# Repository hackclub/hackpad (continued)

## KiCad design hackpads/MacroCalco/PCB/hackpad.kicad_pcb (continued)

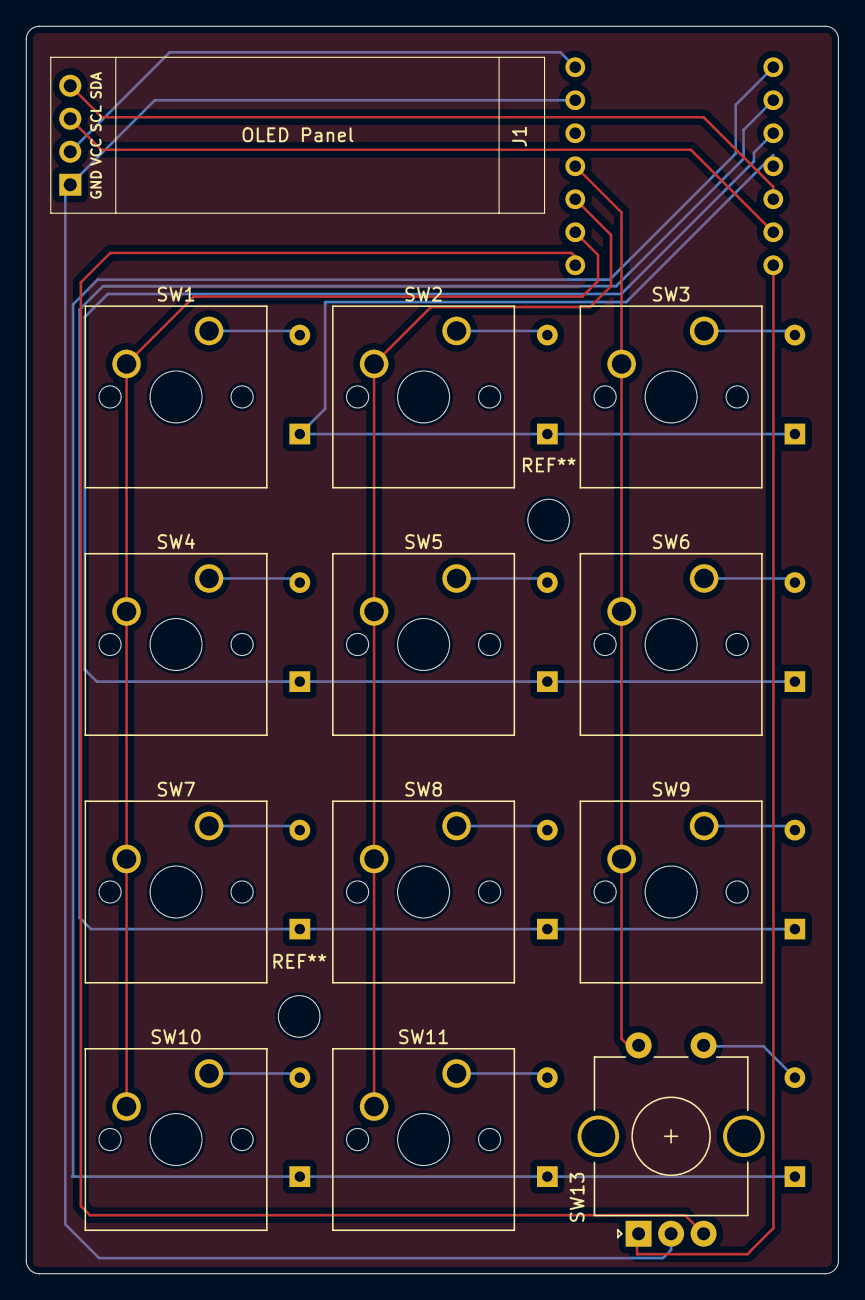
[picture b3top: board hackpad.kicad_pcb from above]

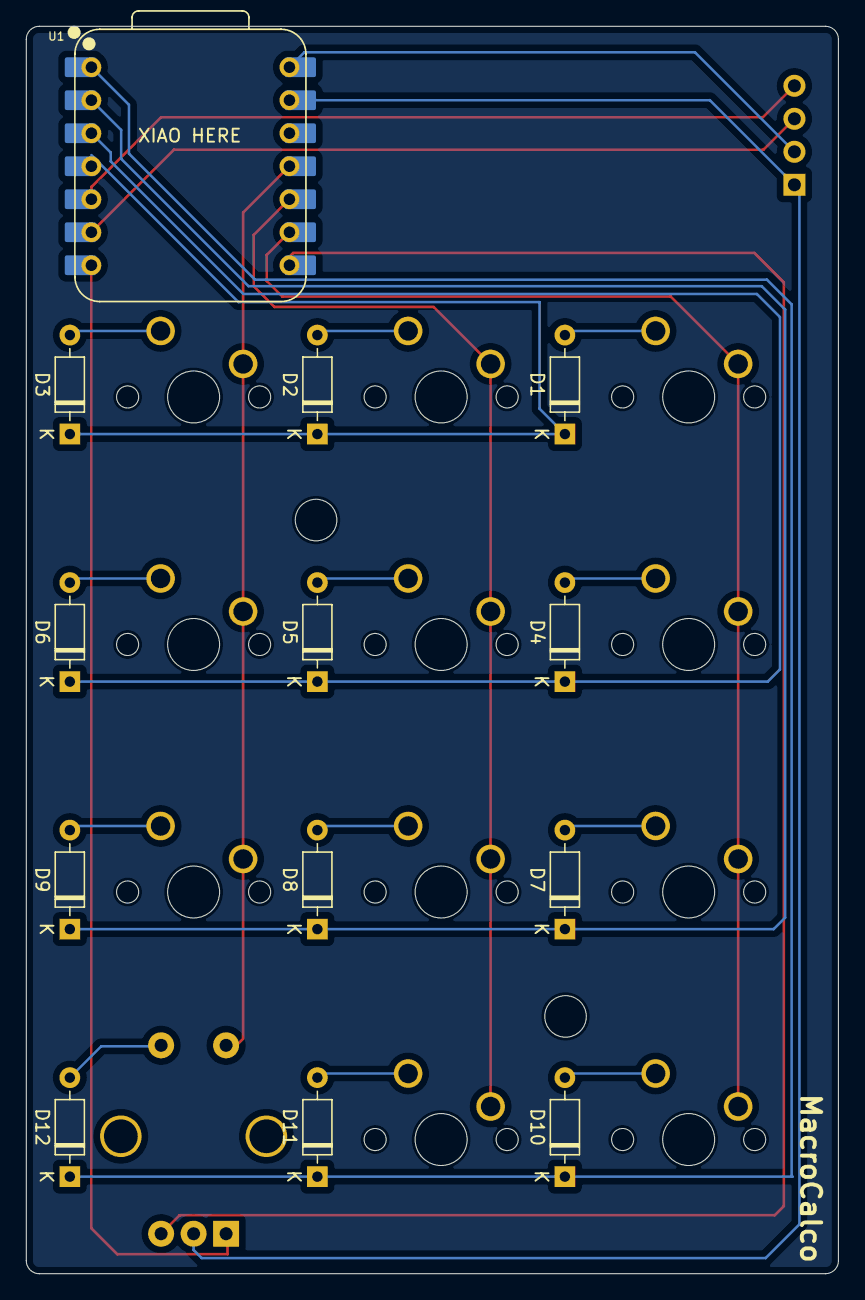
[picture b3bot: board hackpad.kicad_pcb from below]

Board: 2 copper layers, 62.5 x 96.0 mm, 26 parts (13 on the bottom side), 25 nets.

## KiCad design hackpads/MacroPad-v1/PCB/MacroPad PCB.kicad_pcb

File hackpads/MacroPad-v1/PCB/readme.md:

Macropad Project

Overview

This project is a custom macropad featuring 4 buttons and 1 rotary encoder, powered by the XIAO RP2040 microcontroller. It is designed to work with QMK firmware for customizable key mappings and enhanced functionality.

Features

Microcontroller: XIAO RP2040

Inputs: 4 mechanical keys, 1 rotary encoder

Firmware: QMK compatible

Connectivity: USB-C

Customizable: Fully programmable key functions via QMK firmware

Hardware Requirements

XIAO RP2040 microcontroller

4 mechanical key switches

1 rotary encoder with push button

PCB designed in KiCad (MacroPad.kicad_pcb)

USB-C cable for power and programming

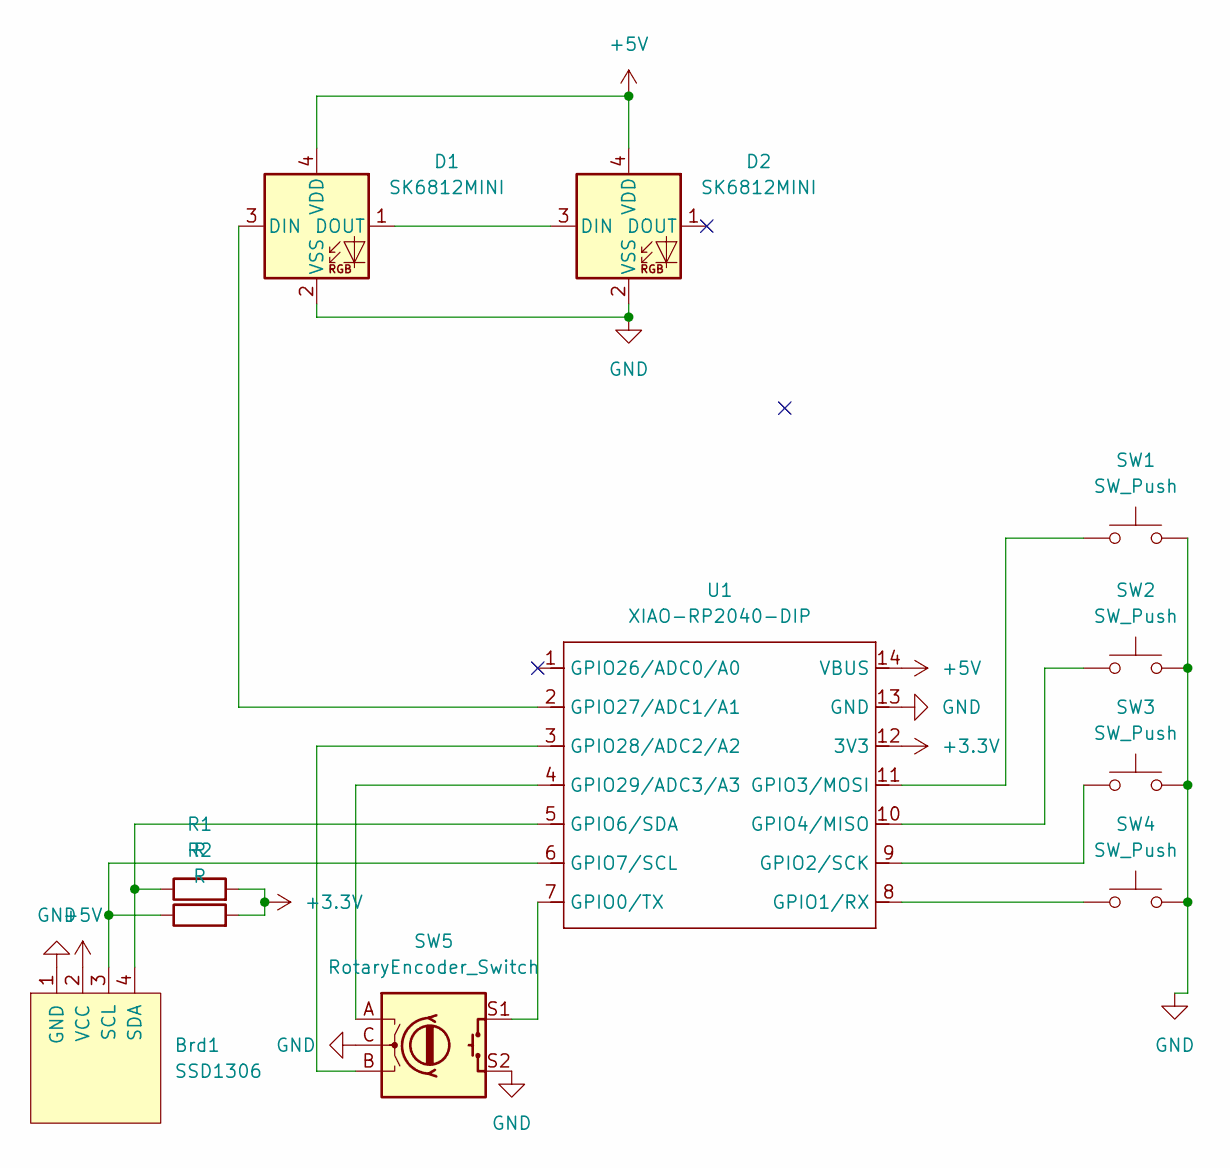
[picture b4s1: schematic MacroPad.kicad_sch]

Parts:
Brd1: SSD1306; 128x64OLED
D1, D2: SK6812MINI; LED_SK6812MINI_PLCC4_3.5x3.5mm_P1.75mm
R1, R2: R; R_Axial_DIN0204_L3.6mm_D1.6mm_P7.62mm_Horizontal
SW1, SW2, SW3, SW4: SW_Push; SW_Cherry_MX_1.00u_PCB
SW5: RotaryEncoder_Switch; RotaryEncoder_Alps_EC11E-Switch_Vertical_H20mm_CircularMoun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
U1: XIAO-RP2040-DIP

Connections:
+3.3V: R1.2, R2.2, U1.12 (3V3)
+5V: Brd1.2 (VCC), D1.4 (VDD), D2.4 (VDD), U1.14 (VBUS)
GND: Brd1.1 (GND), D1.2 (VSS), D2.2 (VSS), SW1.1, SW2.1, SW3.1, SW4.1, SW5.C, SW5.S2, U1.13 (GND)
unnamed: Brd1.3 (SCL), R2.1, U1.6 (GPIO7/SCL)
unnamed: Brd1.4 (SDA), R1.1, U1.5 (GPIO6/SDA)
unnamed: D1.3 (DIN), U1.2 (GPIO27/ADC1/A1)
unnamed: D1.1 (DOUT), D2.3 (DIN)
unnamed: SW5.S1, U1.7 (GPIO0/TX)
unnamed: SW4.2, U1.8 (GPIO1/RX)
unnamed: SW3.2, U1.9 (GPIO2/SCK)
unnamed: SW1.2, U1.11 (GPIO3/MOSI)
unnamed: SW2.2, U1.10 (GPIO4/MISO)
unnamed: SW5.B, U1.3 (GPIO28/ADC2/A2)
unnamed: SW5.A, U1.4 (GPIO29/ADC3/A3)

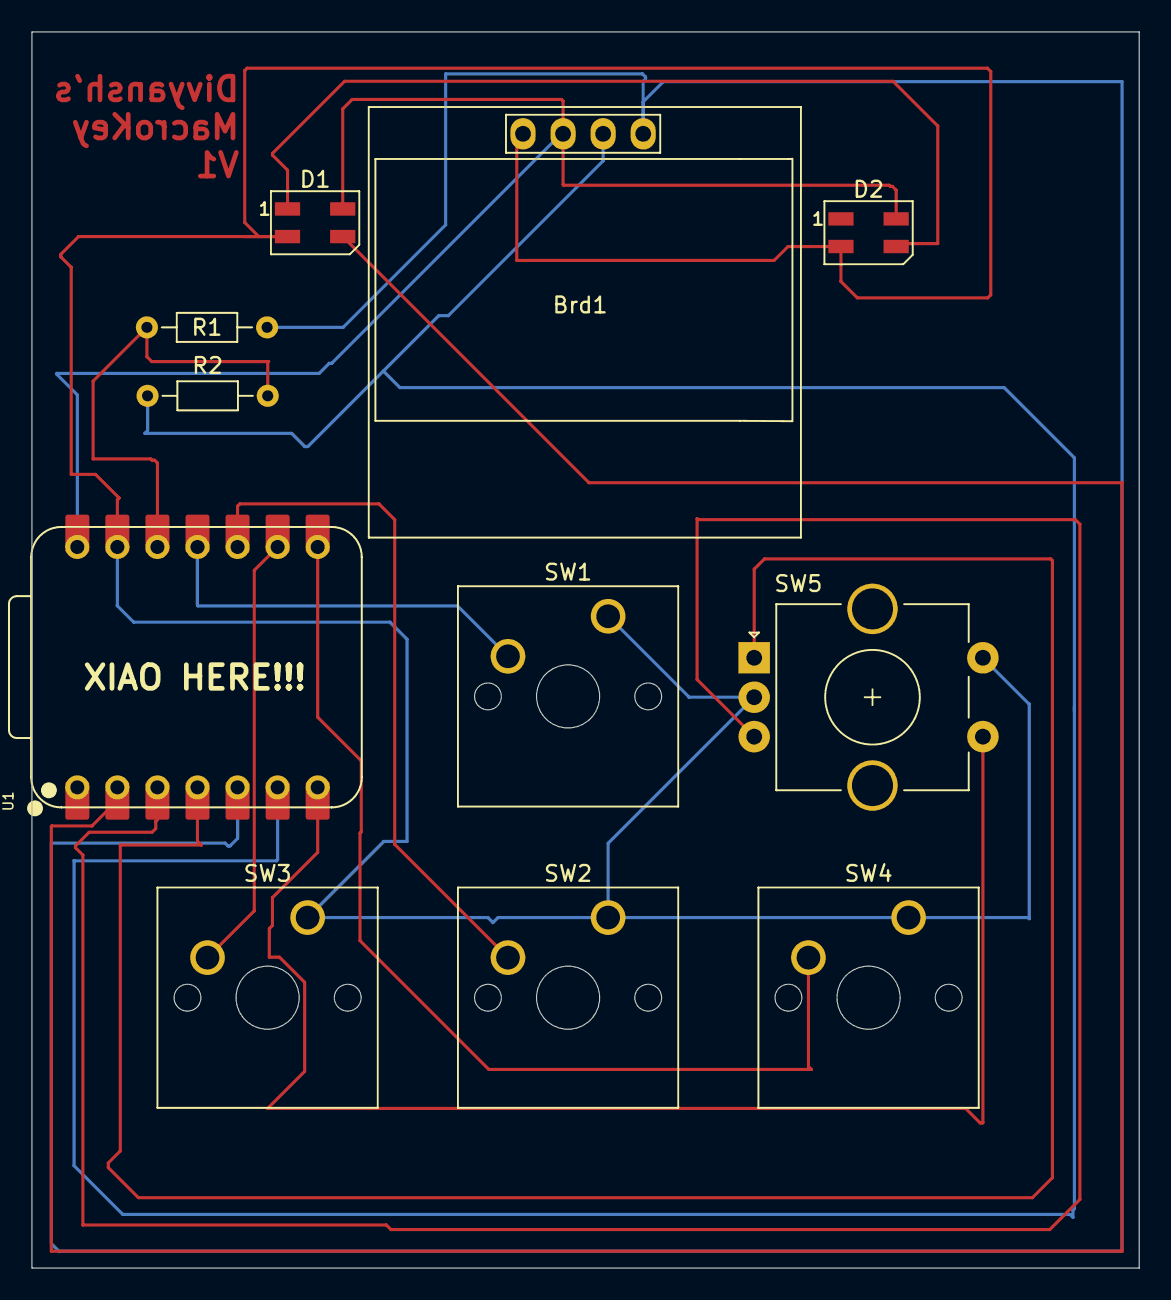
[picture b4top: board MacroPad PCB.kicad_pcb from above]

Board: 2 copper layers, 70.2 x 78.4 mm, 11 parts (0 on the bottom side), 14 nets.

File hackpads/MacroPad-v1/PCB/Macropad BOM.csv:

Reference	Value	Datasheet	Footprint	Qty	DNP
Brd1	SSD1306		SSD1306:128x64OLED	1	
D1,D2	SK6812MINI	https://cdn-shop.adafruit.com/product-files/2686/SK6812MINI_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	LED_SMD:LED_SK6812MINI_PLCC4_3.5x3.5mm_P1.75mm	2	
R1,R2	4.7kΩ	~	Resistor_THT:R_Axial_DIN0204_L3.6mm_D1.6mm_P7.62mm_Horizontal	2	
SW1,SW2,SW3,SW4	SW_Push	~	Button_Switch_Keyboard:SW_Cherry_MX_1.00u_PCB	4	
SW5	RotaryEncoder_Switch	~	Rotary_Encoder:RotaryEncoder_Alps_EC11E-Switch_Vertical_H20mm_CircularMountingHoles	1	
U1	XIAO-RP2040-DIP		OPL:XIAO-RP2040-DIP	1

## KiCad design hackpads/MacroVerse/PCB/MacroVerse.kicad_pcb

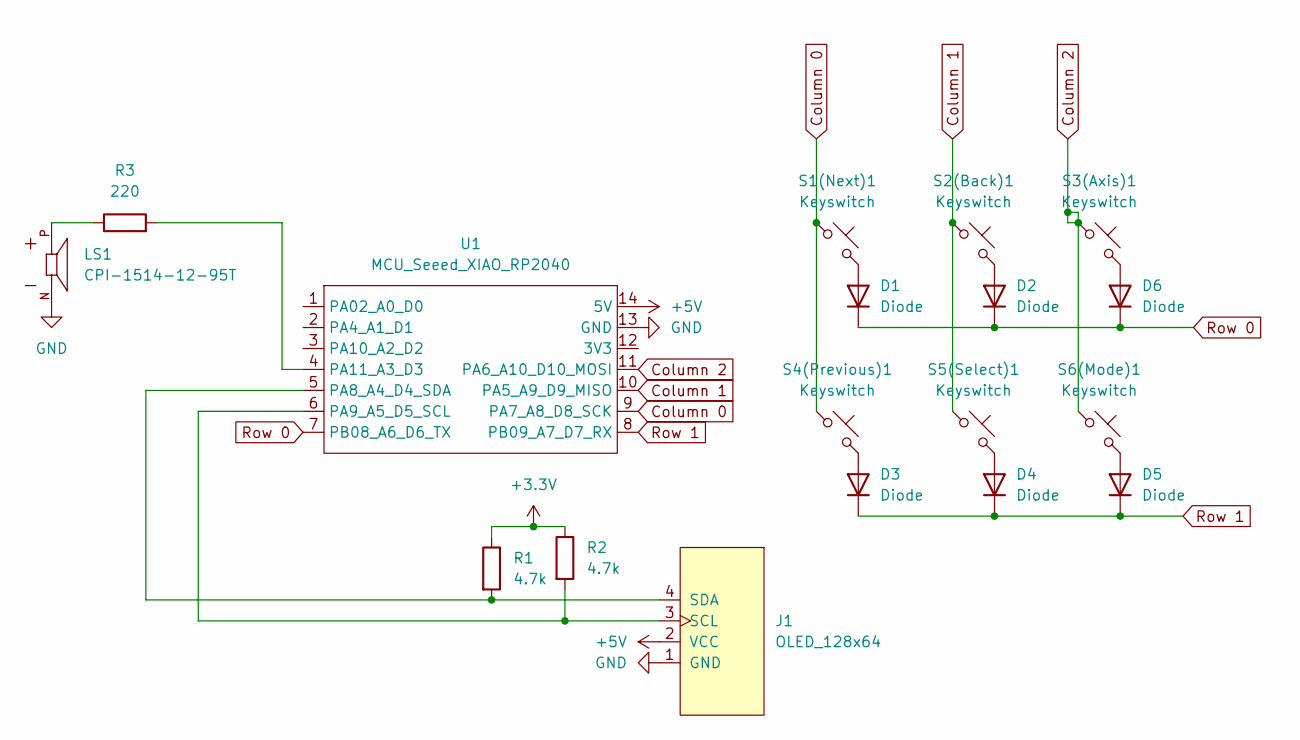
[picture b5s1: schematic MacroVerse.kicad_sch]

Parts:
D1, D2, D3, D4, D5, D6: Diode; Diode_DO-35
J1: OLED_128x64
LS1: CPI-1514-12-95T; XDCR_CPI-1514-12-95T; PARTREV 1.0
R1, R2: 4.7k; R_Axial_DIN0207_L6.3mm_D2.5mm_P7.62mm_Horizontal
R3: 220; R_Axial_DIN0207_L6.3mm_D2.5mm_P7.62mm_Horizontal
S1(Next)1, S2(Back)1, S3(Axis)1, S4(Previous)1, S5(Select)1, S6(Mode)1: Keyswitch; MX_PCB_1.00u
U1: MCU_Seeed_XIAO_RP2040; Seeed_XIAO_RP2040

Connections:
+3.3V: R1.1, R2.1
+5V: J1.2 (VCC), U1.14 (5V)
Column 0: S1(Next)1.1, S4(Previous)1.1, U1.9 (PA7_A8_D8_SCK)
Column 1: S2(Back)1.1, S5(Select)1.1, U1.10 (PA5_A9_D9_MISO)
Column 2: S3(Axis)1.1, S6(Mode)1.1, U1.11 (PA6_A10_D10_MOSI)
GND: J1.1 (GND), LS1.N, U1.13 (GND)
unnamed: D1.2 (A), S1(Next)1.2
unnamed: D2.2 (A), S2(Back)1.2
unnamed: D3.2 (A), S4(Previous)1.2
unnamed: D4.2 (A), S5(Select)1.2
unnamed: D5.2 (A), S6(Mode)1.2
unnamed: D6.2 (A), S3(Axis)1.2
unnamed: J1.3 (SCL), R2.2, U1.6 (PA9_A5_D5_SCL)
unnamed: J1.4 (SDA), R1.2, U1.5 (PA8_A4_D4_SDA)
unnamed: LS1.P, R3.1
unnamed: R3.2, U1.4 (PA11_A3_D3)
Row 0: D1.1 (K), D2.1 (K), D6.1 (K), U1.7 (PB08_A6_D6_TX)
Row 1: D3.1 (K), D4.1 (K), D5.1 (K), U1.8 (PB09_A7_D7_RX)

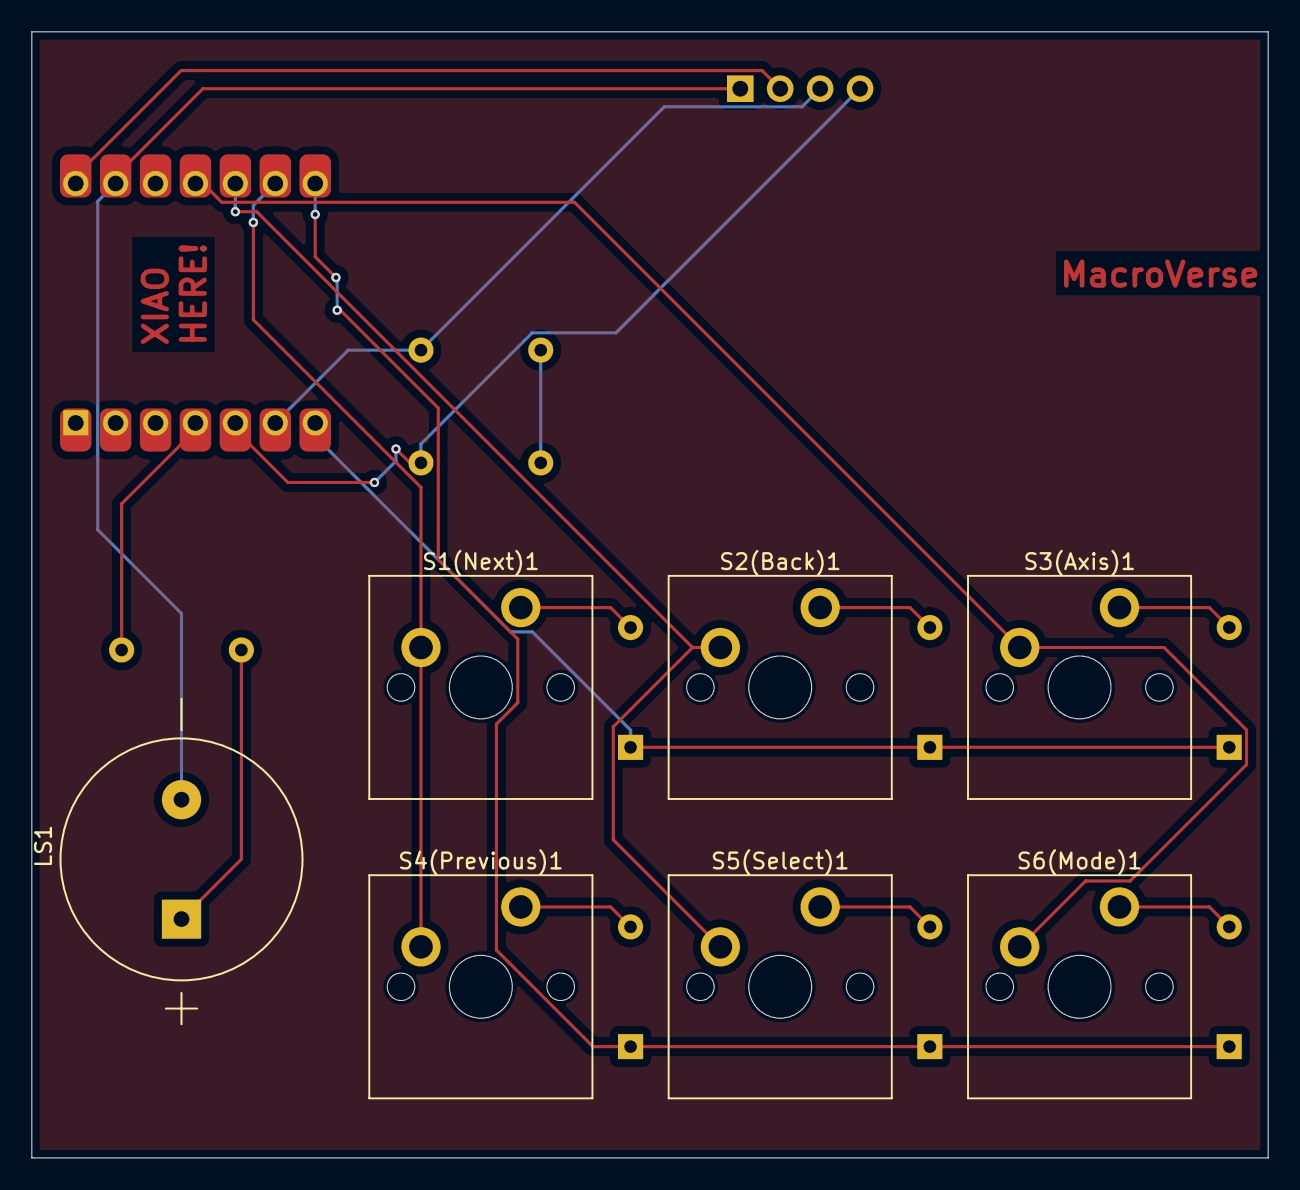
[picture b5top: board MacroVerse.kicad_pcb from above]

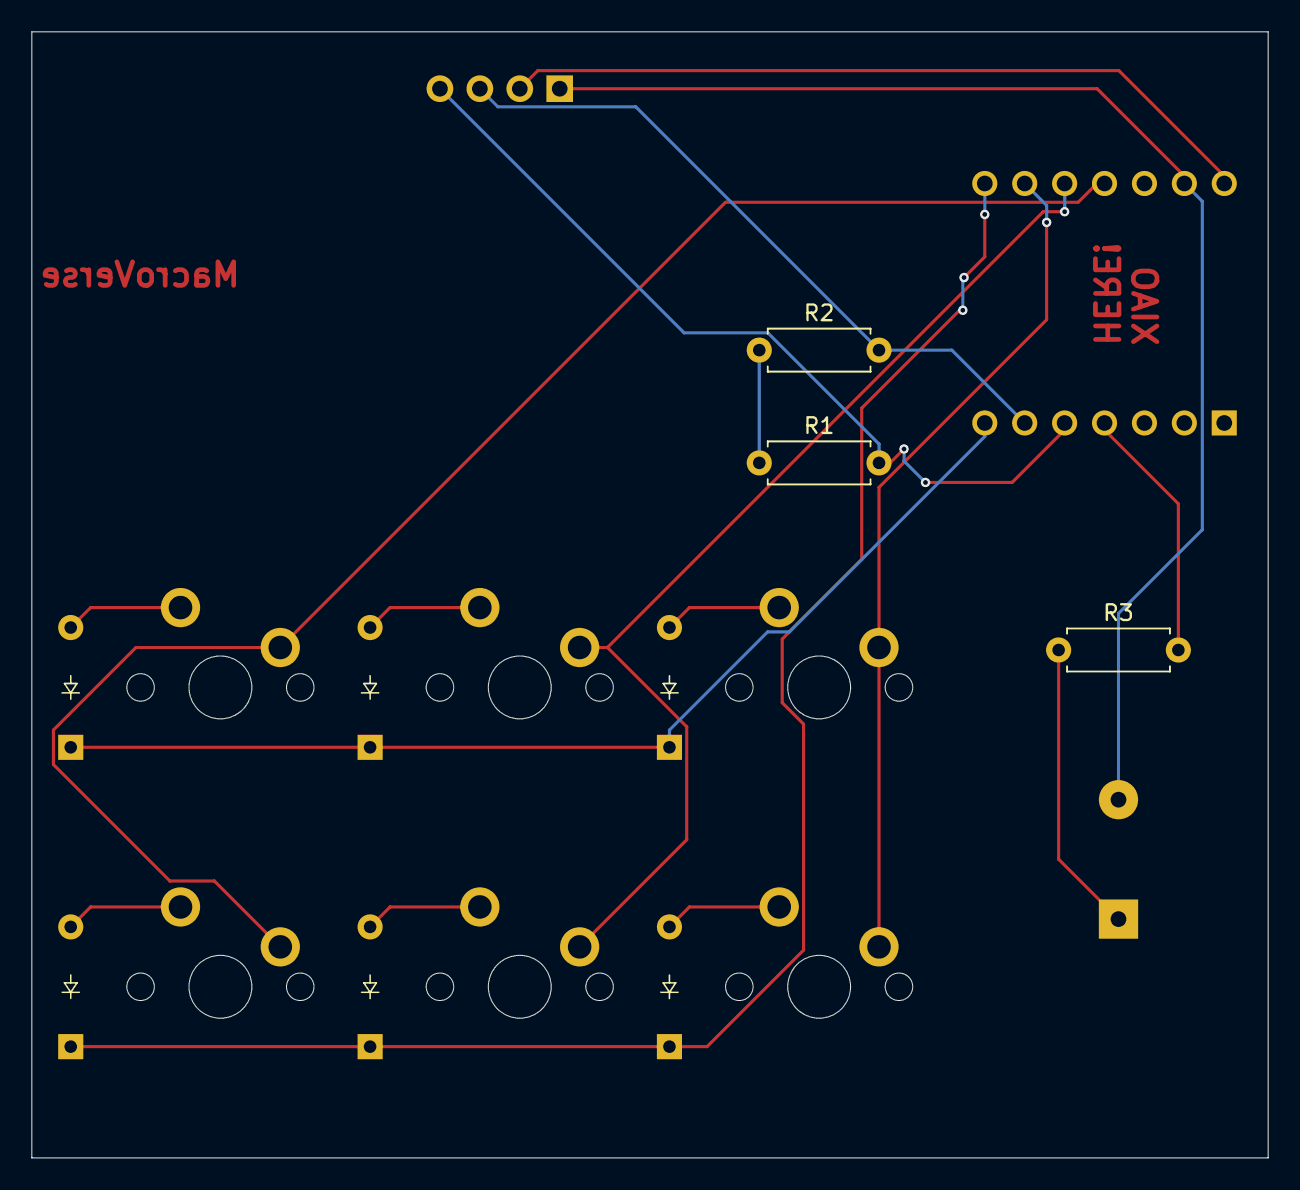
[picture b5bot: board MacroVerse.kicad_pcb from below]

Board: 2 copper layers, 78.7 x 71.7 mm, 18 parts (9 on the bottom side), 18 nets.

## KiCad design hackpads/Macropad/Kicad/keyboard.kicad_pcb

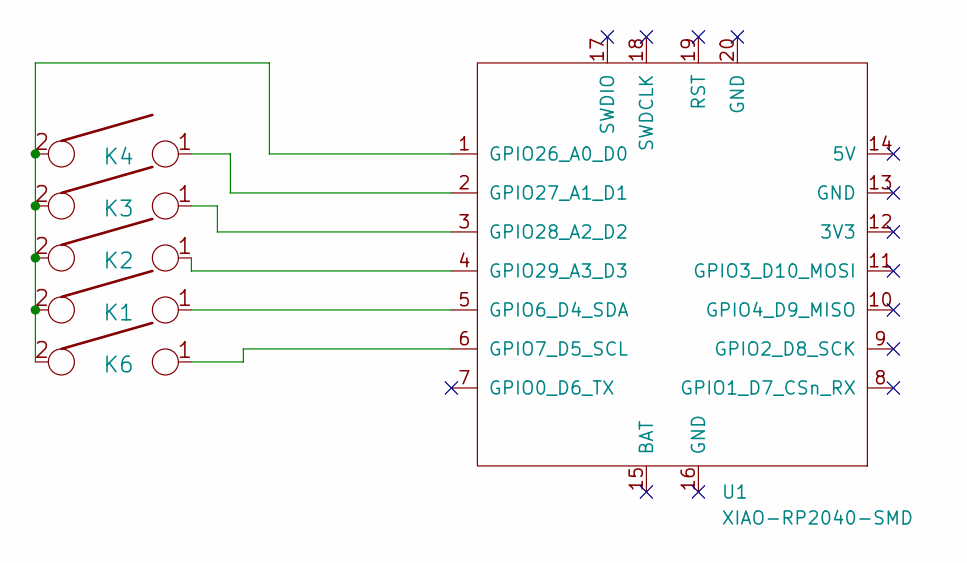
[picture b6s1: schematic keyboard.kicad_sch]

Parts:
K1, K2, K3, K4, K6: KEYSW; SW_Cherry_MX_1.00u_Plate
U1: XIAO-RP2040-SMD; XIAO-RP2350-DIP

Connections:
unnamed: K1.1, U1.5 (GPIO6_D4_SDA)
unnamed: K6.1, U1.6 (GPIO7_D5_SCL)
unnamed: K1.2, K2.2, K3.2, K4.2, K6.2, U1.1 (GPIO26_A0_D0)
unnamed: K4.1, U1.2 (GPIO27_A1_D1)
unnamed: K3.1, U1.3 (GPIO28_A2_D2)
unnamed: K2.1, U1.4 (GPIO29_A3_D3)

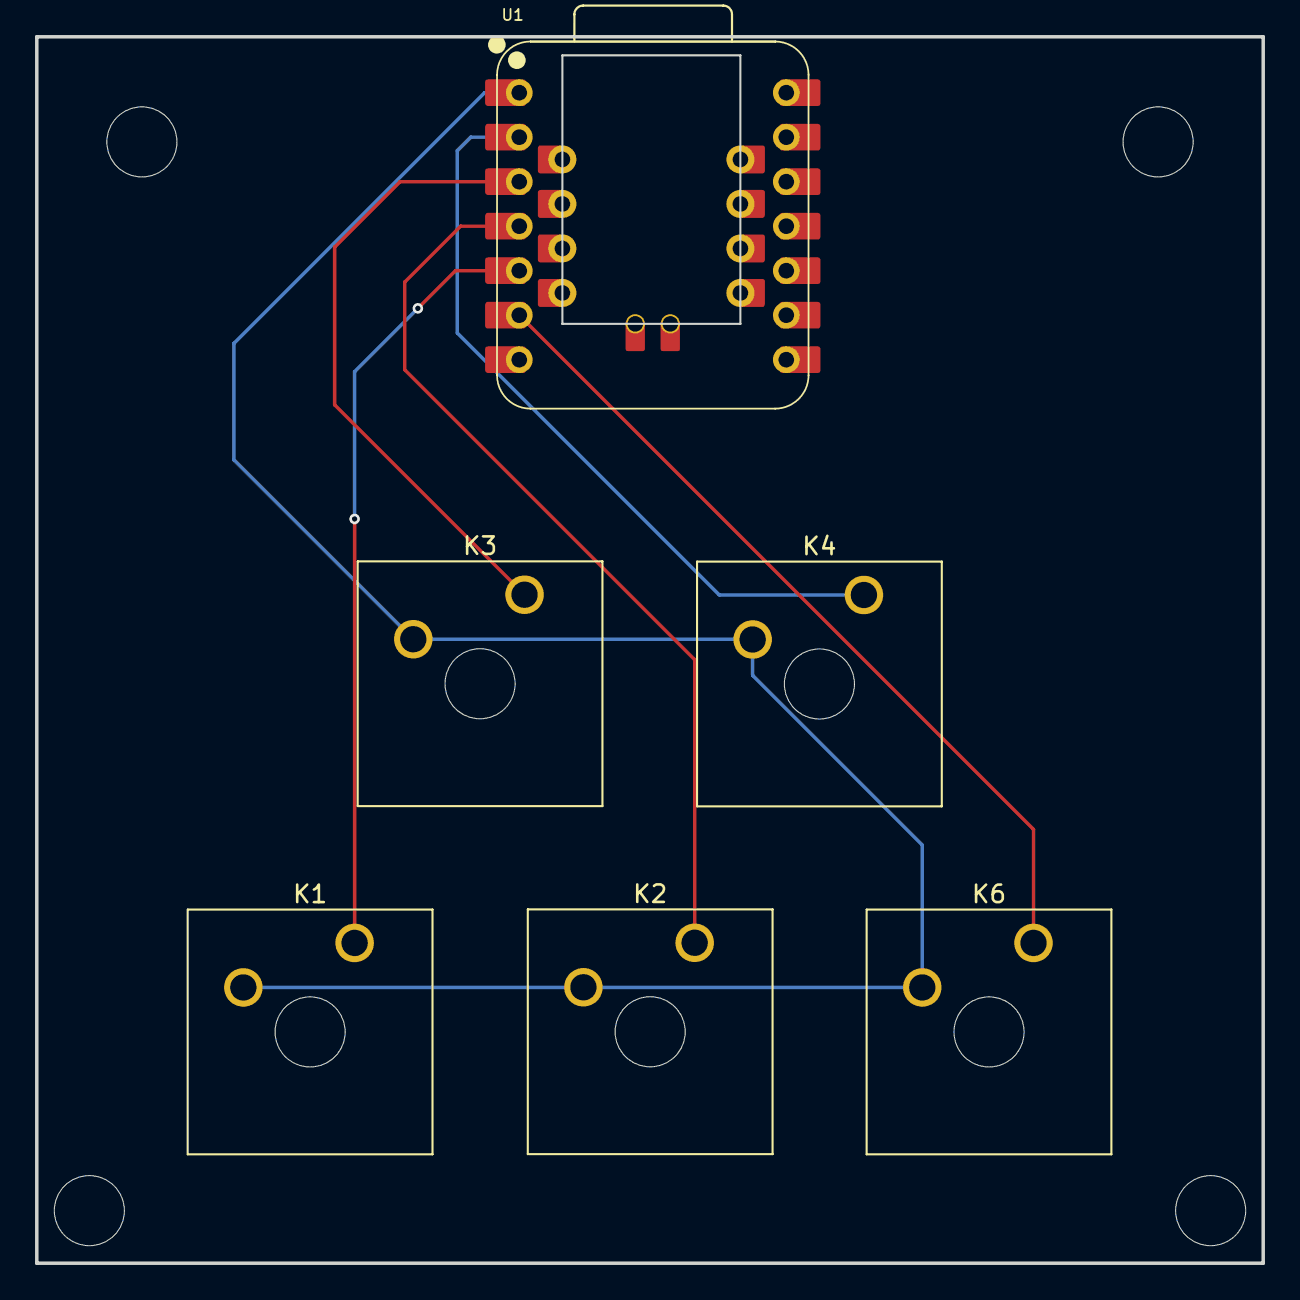
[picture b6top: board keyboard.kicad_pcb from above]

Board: 2 copper layers, 70.0 x 70.0 mm, 6 parts (0 on the bottom side), 6 nets.
